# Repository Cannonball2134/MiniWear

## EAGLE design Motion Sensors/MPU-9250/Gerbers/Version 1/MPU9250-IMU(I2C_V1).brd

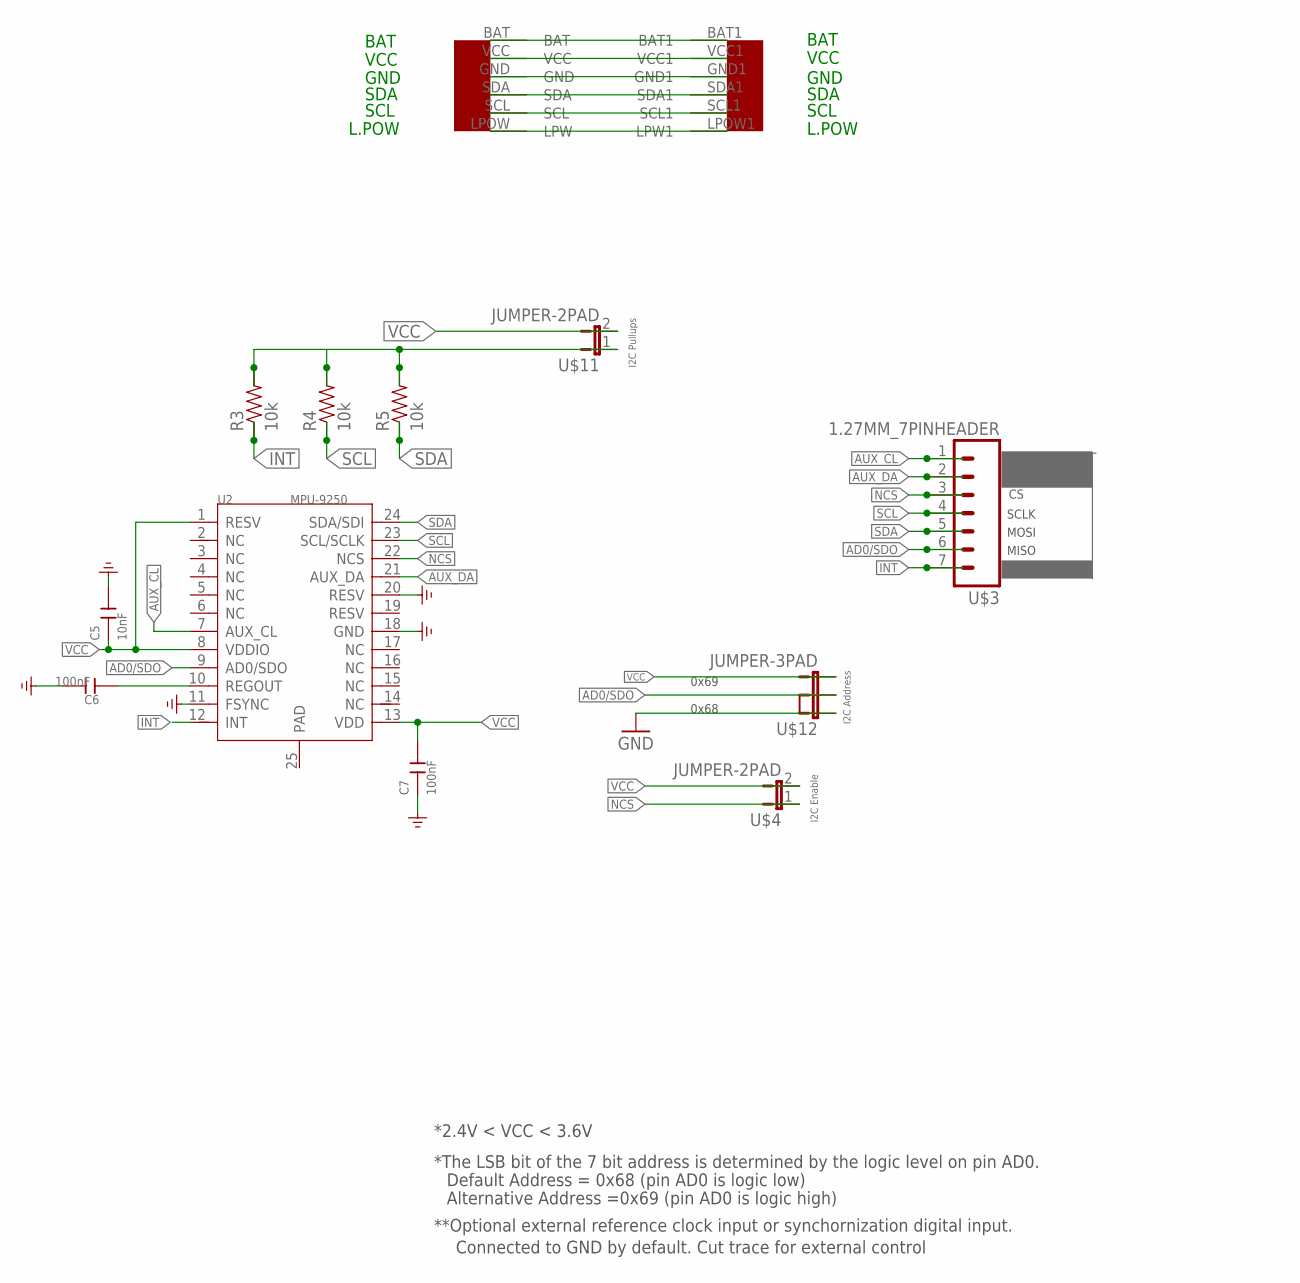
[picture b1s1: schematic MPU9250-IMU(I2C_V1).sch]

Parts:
C5: 10nF; C0603
C6, C7: 100nF; C0603
R3, R4, R5: 10k; 0402-RES
U2: MPU-9250; LEAD-QFN24
U$1: EZ-I2CHEADERV1
U$3: 1.27MM_7PINHEADER
U$4, U$11: JUMPER-2PAD
U$12: JUMPER-3PAD

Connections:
AD0/SDO: U2.9 (AD0/SDO), U$3.6, U$12.2
AUX_CL: U2.7 (AUX_CL), U$3.1
AUX_DA: U2.21 (AUX_DA), U$3.2
BAT: U$1.BAT, U$1.BAT1
GND: C5.2, C6.2, C7.1, U2.11 (FSYNC), U2.18 (GND), U2.20 (RESV), U$1.GND, U$1.GND1, U$12.1
INT: R3.1, U2.12 (INT), U$3.7
unnamed: C6.1, U2.10 (REGOUT)
unnamed: U$1.LPOW (LPW), U$1.LPOW1 (LPW1)
unnamed: R3.2, R4.2, R5.2, U$11.1
NCS: U2.22 (NCS), U$3.3, U$4.1
SCL: R4.1, U2.23 (SCL/SCLK), U$1.SCL, U$1.SCL1, U$3.4
SDA: R5.1, U2.24 (SDA/SDI), U$1.SDA, U$1.SDA1, U$3.5
VCC: C5.1, C7.2, U2.1 (RESV), U2.8 (VDDIO), U2.13 (VDD), U$1.VCC, U$1.VCC1, U$4.2, U$11.2, U$12.3

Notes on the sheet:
**Optional external reference clock input or synchornization digital input.
Connected to GND by default. Cut trace for external control
Default Address = 0x68 (pin AD0 is logic low)
Alternative Address =0x69 (pin AD0 is logic high)
*The LSB bit of the 7 bit address is determined by the logic level on pin AD0.
*2.4V < VCC < 3.6V
VCC
GND
SDA
SCL
BAT
L.POW
0x69
0x68
SCLK
MOSI
MISO
I2C Address
I2C Enable
I2C Pullups

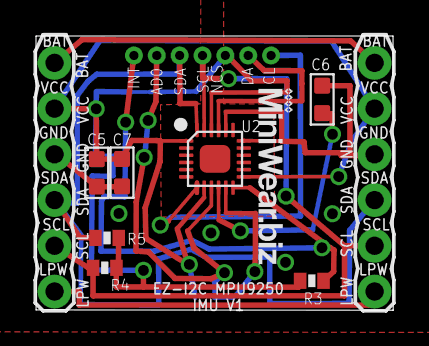
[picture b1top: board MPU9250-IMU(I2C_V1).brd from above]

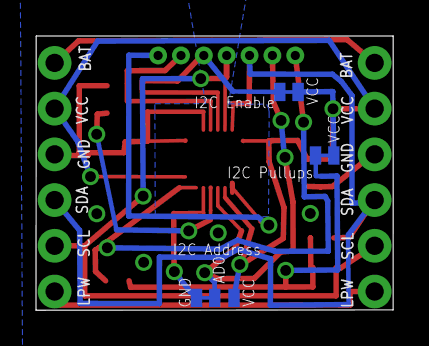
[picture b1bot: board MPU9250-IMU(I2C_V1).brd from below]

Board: 2 copper layers, 19.8 x 15.2 mm, 13 parts (3 on the bottom side), 13 nets.

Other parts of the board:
U$2: LOGO2

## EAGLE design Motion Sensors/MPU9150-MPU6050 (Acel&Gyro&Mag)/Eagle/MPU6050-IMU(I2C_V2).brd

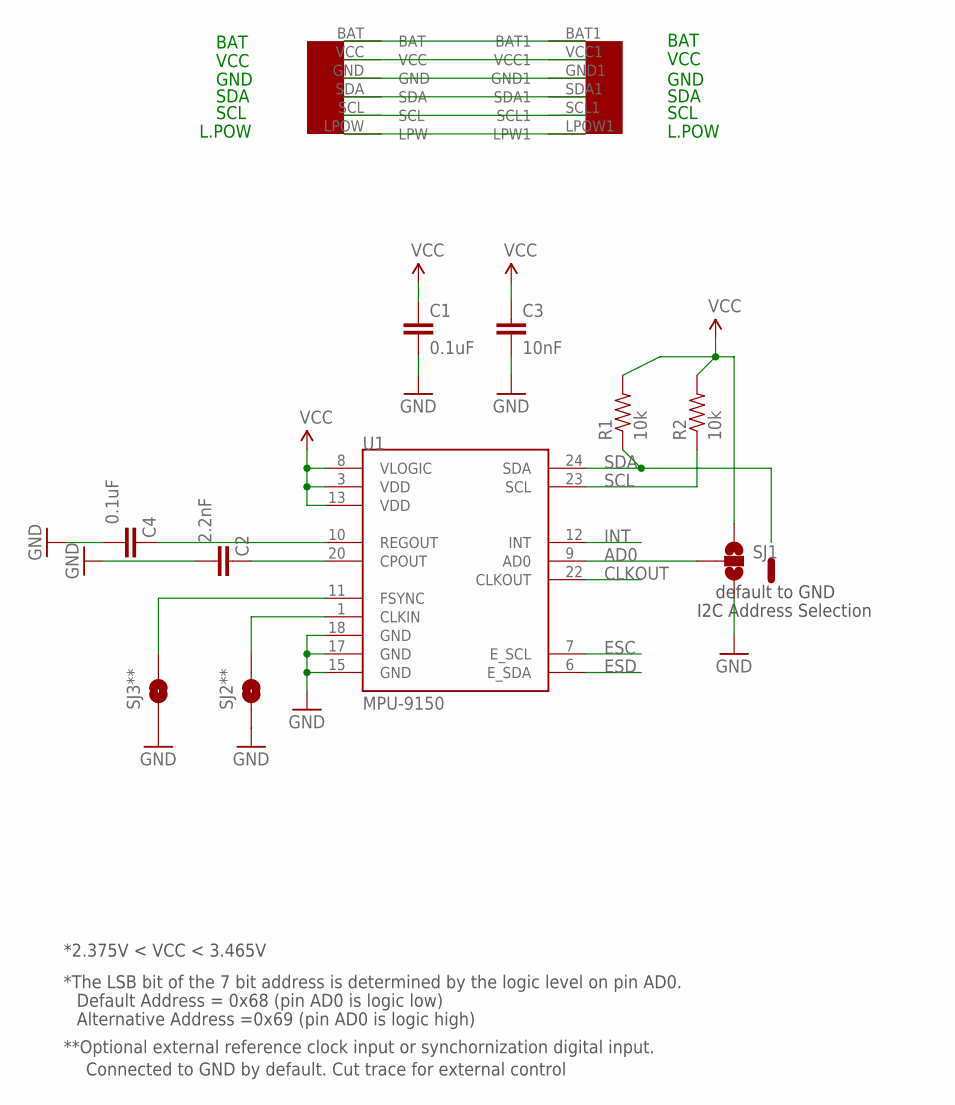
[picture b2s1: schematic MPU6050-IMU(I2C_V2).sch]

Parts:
C1, C4: 0.1uF; 0402-CAP; MPN 02016D104KAT2A
C2: 2.2nF; 0402-CAP; MPN 06035C222KAT2A
C3: 10nF; 0402-CAP; MPN 06035G103ZAT2A
R1, R2: 10k; 0402-RES
SJ1: SOLDERJUMPER_2WAYPASTE2&3; SJ_3_PASTE2&3
SJ2**, SJ3**: SOLDERJUMPERTRACE; SJ_2S-TRACE
U1: MPU-9150; QFN-24-NP
U$1: EZ-I2CHEADERV1

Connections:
AD0: SJ1.2, U1.9 (AD0)
BAT: U$1.BAT, U$1.BAT1
CLKIN: SJ2**.2, U1.1 (CLKIN)
CLKOUT: U1.22 (CLKOUT)
ESC: U1.7 (E_SCL)
ESD: U1.6 (E_SDA)
FSYNC: SJ3**.2, U1.11 (FSYNC)
GND: C1.2, C2.2, C3.2, C4.2, SJ1.3, SJ2**.1, SJ3**.1, U1.15 (GND), U1.17 (GND), U1.18 (GND), U$1.GND, U$1.GND1
INT: U1.12 (INT)
unnamed: C2.1, U1.20 (CPOUT)
unnamed: C4.1, U1.10 (REGOUT)
unnamed: U$1.LPOW (LPW), U$1.LPOW1 (LPW1)
SCL: R2.1, U1.23 (SCL), U$1.SCL, U$1.SCL1
SDA: R1.1, U1.24 (SDA), U$1.SDA, U$1.SDA1
VCC: C1.1, C3.1, R1.2, R2.2, SJ1.1, U1.3 (VDD), U1.8 (VLOGIC), U1.13 (VDD), U$1.VCC, U$1.VCC1

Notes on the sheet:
I2C Address Selection
**Optional external reference clock input or synchornization digital input.
Connected to GND by default. Cut trace for external control
Default Address = 0x68 (pin AD0 is logic low)
Alternative Address =0x69 (pin AD0 is logic high)
*The LSB bit of the 7 bit address is determined by the logic level on pin AD0.
default to GND
*2.375V < VCC < 3.465V
VCC
GND
SDA
SCL
BAT
L.POW

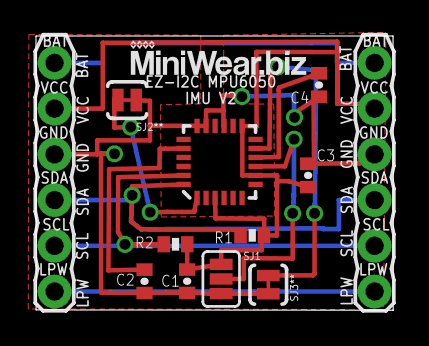
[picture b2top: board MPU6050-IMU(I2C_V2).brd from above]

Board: 2 copper layers, 19.8 x 15.2 mm, 12 parts (0 on the bottom side), 11 nets.

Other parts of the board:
U$2: LOGO2

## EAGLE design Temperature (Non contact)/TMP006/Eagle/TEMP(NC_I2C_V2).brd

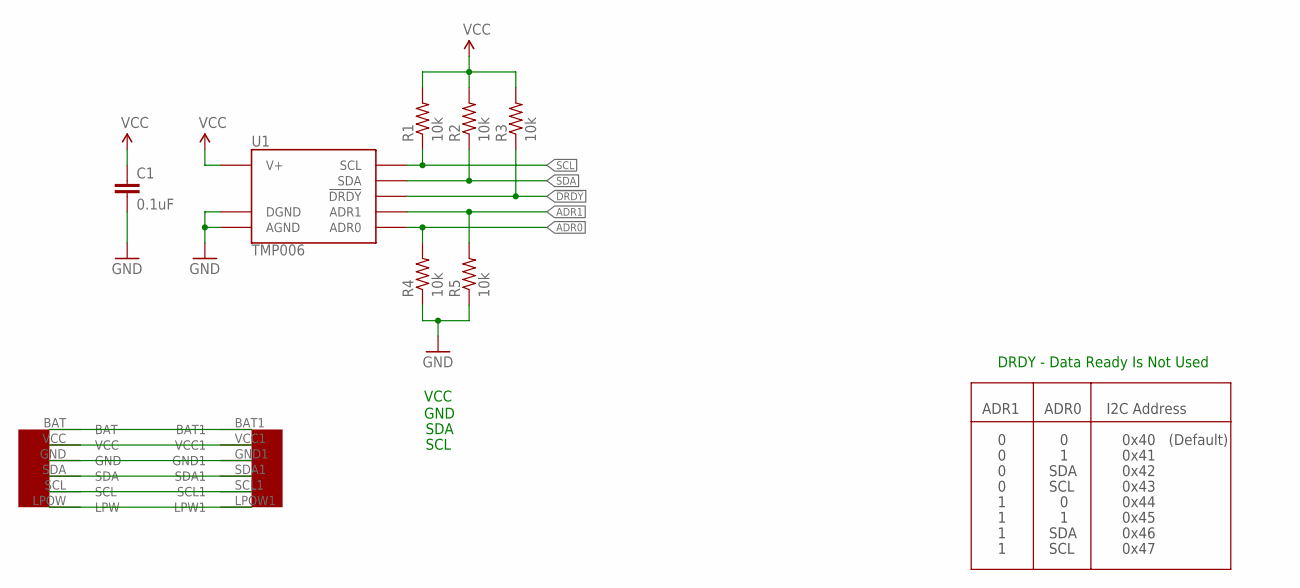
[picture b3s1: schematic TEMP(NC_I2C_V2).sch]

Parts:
C1: 0.1uF; 0603-CAP
R1, R2, R3, R4, R5: 10k; 0603-RES
U1: TMP006; BGA8DS
U$1: EZ-I2CHEADERV1

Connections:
!DRDY: R3.1, U1.C2 (!DRDY)
ADR0: R4.2, U1.C1 (ADR0)
ADR1: R5.2, U1.B1 (ADR1)
GND: C1.2, R4.1, R5.1, U1.A1 (DGND), U1.A2 (AGND), U$1.GND, U$1.GND1
unnamed: U$1.BAT, U$1.BAT1
unnamed: U$1.LPOW (LPW), U$1.LPOW1 (LPW1)
SCL: R1.1, U1.B3 (SCL), U$1.SCL, U$1.SCL1
SDA: R2.1, U1.C3 (SDA), U$1.SDA, U$1.SDA1
VCC: C1.1, R1.2, R2.2, R3.2, U1.A3 (V+), U$1.VCC, U$1.VCC1

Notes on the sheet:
ADR1
ADR0
I2C Address
SDA
SCL
0x40
0x41
0x42
0x43
0x44
0x45
0x46
0x47
(Default)
VCC
GND
DRDY - Data Ready Is Not Used

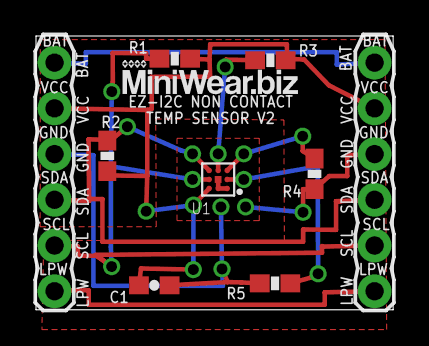
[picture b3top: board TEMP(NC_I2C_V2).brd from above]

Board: 2 copper layers, 19.8 x 15.2 mm, 9 parts (0 on the bottom side), 9 nets.

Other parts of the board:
U$2: LOGO2

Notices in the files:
parts and their libraries:
SparkFun-Passives: Licensing: CC v3.0 Share-Alike You are welcome to use this library for commercial purposes.
